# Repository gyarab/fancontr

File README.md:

# Rozcestník

- `dokumentace.pdf` -- Dokumentace v PDF
- `dokumentace/` -- Zdrojové soubory dokumentace
- `hw_foto/` -- Fotodokumentace hardwaru
- `firmware/` -- Zdrojový kód firmwaru
- `kicad_v1/` -- KiCad projekt hardwaru v1
	- `kicad_v1/fancontr.pdf` -- PDF schématu
	- `kicad_v1/bom/ibom.html` -- Interaktivní zobrazení tištěného spoje
- `kicad_v2_wip/` -- KiCad projekt hardwaru v2 (nefinální!)
	- `kicad_v2_wip/fancontr.pdf` -- PDF schématu
	- `kicad_v2_wip/bom/ibom.html` -- Interaktivní zobrazení tištěného spoje

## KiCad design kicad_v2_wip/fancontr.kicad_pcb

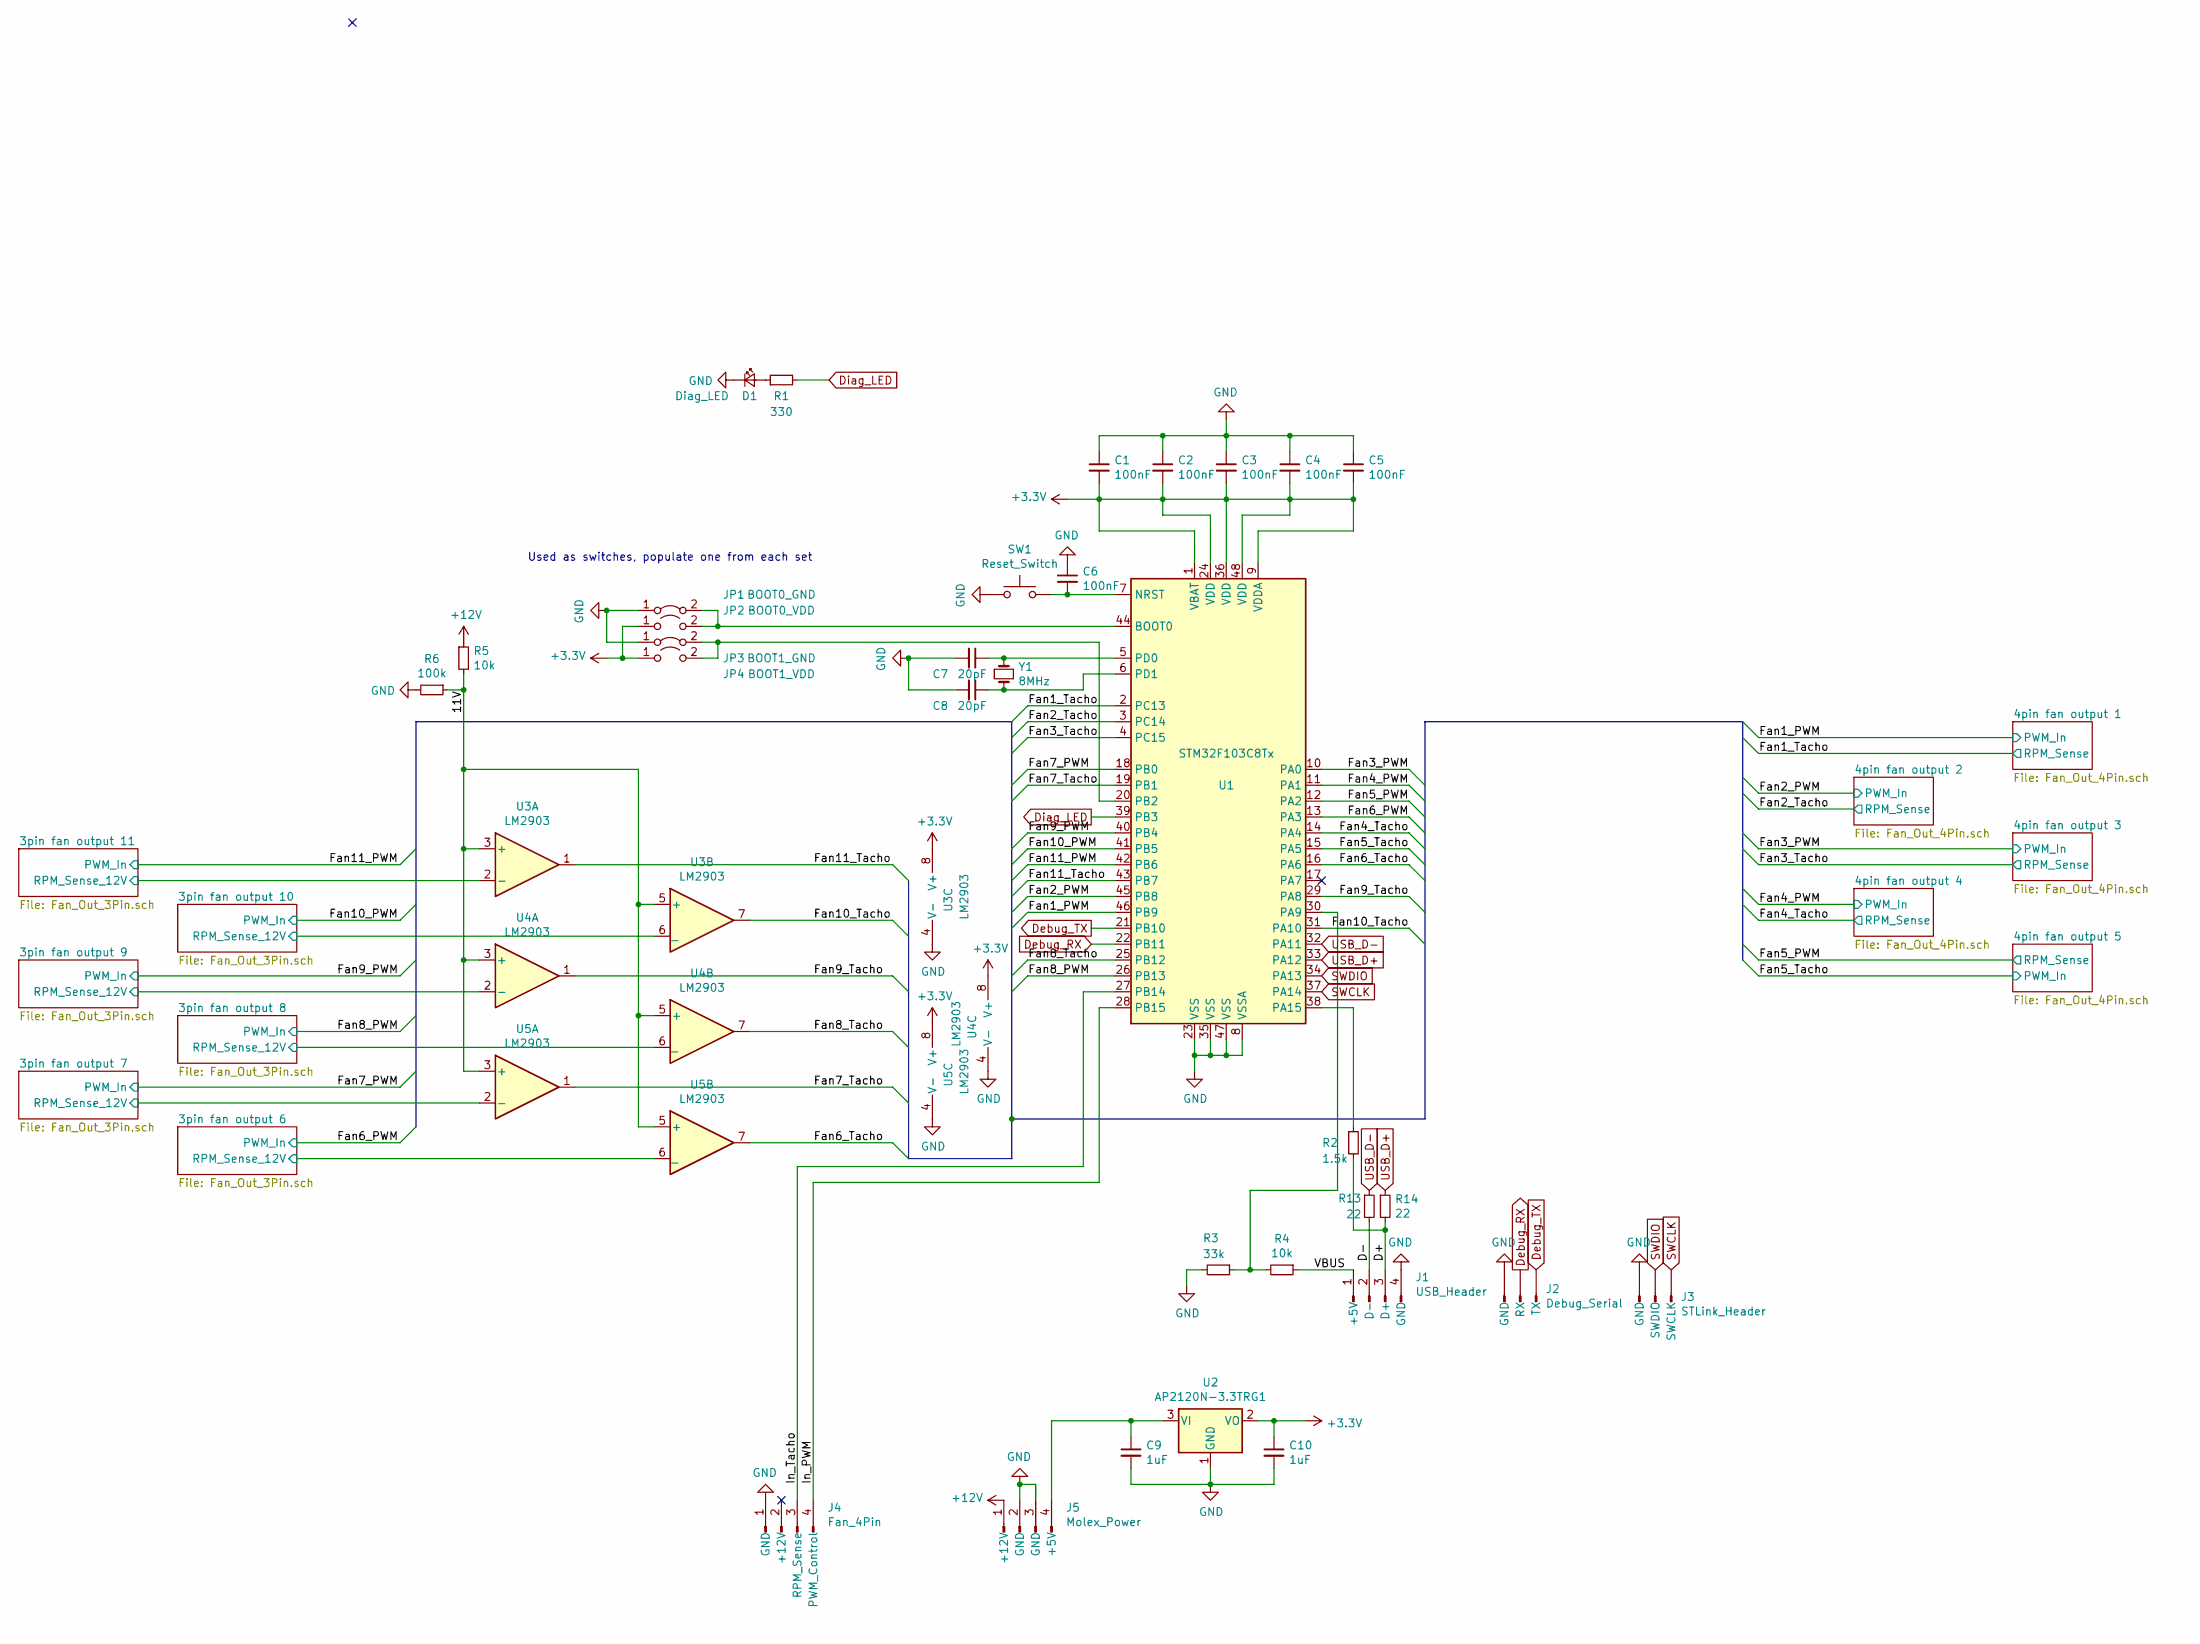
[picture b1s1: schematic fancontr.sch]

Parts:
C1, C2, C3, C4, C5, C6: 100nF; C_0805_2012Metric_Pad1.15x1.40mm_HandSolder
C7, C8: 20pF; C_0805_2012Metric_Pad1.15x1.40mm_HandSolder
C9, C10: 1uF; C_0805_2012Metric_Pad1.15x1.40mm_HandSolder
D1: Diag_LED; LED_0805_2012Metric_Castellated
J1: USB_Header; PinHeader_1x04_P2.54mm_Horizontal_NoSilk
J2: Debug_Serial; PinHeader_1x03_P2.54mm_Vertical
J3: STLink_Header; PinHeader_1x03_P2.54mm_Vertical
J4: Fan_4Pin; PinHeader_1x04_P2.54mm_Horizontal_NoSilk
J5: Molex_Power; MATE-N-LOK 641737-1
JP1: BOOT0_GND; SolderJumper-2_P1.3mm_Open_Pad1.0x1.5mm
JP2: BOOT0_VDD; SolderJumper-2_P1.3mm_Open_Pad1.0x1.5mm
JP3: BOOT1_GND; SolderJumper-2_P1.3mm_Open_Pad1.0x1.5mm
JP4: BOOT1_VDD; SolderJumper-2_P1.3mm_Open_Pad1.0x1.5mm
R1: 330; R_0805_2012Metric_Pad1.15x1.40mm_HandSolder
R2: 1.5k; R_0805_2012Metric_Pad1.15x1.40mm_HandSolder
R3: 33k; R_0805_2012Metric_Pad1.15x1.40mm_HandSolder
R4, R5: 10k; R_0805_2012Metric_Pad1.15x1.40mm_HandSolder
R6: 100k; R_0805_2012Metric_Pad1.15x1.40mm_HandSolder
R13, R14: 22; R_0805_2012Metric_Pad1.15x1.40mm_HandSolder
SW1: Reset_Switch; SolderJumper-2_P1.3mm_Open_Pad1.0x1.5mm
U1: STM32F103C8Tx; LQFP-48_7x7mm_P0.5mm
U2: AP2120N-3.3TRG1; SOT-23_Handsoldering
U3, U4, U5: LM2903; SOIC-8_3.9x4.9mm_P1.27mm
Y1: 8MHz; Crystal_SMD_HC49-SD

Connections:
+3V3: C1.2, C2.2, C3.2, C4.2, C5.2, C10.1, JP2.1 (A), JP4.1 (A), U1.1 (VBAT), U1.9 (VDDA), U1.24 (VDD), U1.36 (VDD), U1.48 (VDD), U2.2 (VO), U3.8 (V+), U4.8 (V+), U5.8 (V+)
+12V: J5.1 (+12V), R5.1; also elsewhere on the board
/3pin fan output 6/RPM_Sense_12V: U5.6 (_); also elsewhere on the board
/3pin fan output 7/RPM_Sense_12V: U5.2 (-); also elsewhere on the board
/3pin fan output 8/RPM_Sense_12V: U4.6 (_); also elsewhere on the board
/3pin fan output 9/RPM_Sense_12V: U4.2 (-); also elsewhere on the board
/3pin fan output 10/RPM_Sense_12V: U3.6 (_); also elsewhere on the board
/3pin fan output 11/RPM_Sense_12V: U3.2 (-); also elsewhere on the board
/11V: R5.2, R6.1, U3.3 (+), U3.5 (+), U4.3 (+), U4.5 (+), U5.3 (+), U5.5 (+)
/D+: J1.3 (D+), R2.2, R14.2
/D-: J1.2 (D-), R13.2
/Fan1_PWM: U1.46 (PB9); also elsewhere on the board
/Fan1_Tacho: U1.2 (PC13); also elsewhere on the board
/Fan2_PWM: U1.45 (PB8); also elsewhere on the board
/Fan2_Tacho: U1.3 (PC14); also elsewhere on the board
/Fan3_PWM: U1.10 (PA0); also elsewhere on the board
/Fan3_Tacho: U1.4 (PC15); also elsewhere on the board
/Fan4_PWM: U1.11 (PA1); also elsewhere on the board
/Fan4_Tacho: U1.14 (PA4); also elsewhere on the board
/Fan5_PWM: U1.12 (PA2); also elsewhere on the board
/Fan5_Tacho: U1.15 (PA5); also elsewhere on the board
/Fan6_PWM: U1.13 (PA3); also elsewhere on the board
/Fan6_Tacho: U1.16 (PA6), U5.7
/Fan7_PWM: U1.18 (PB0); also elsewhere on the board
/Fan7_Tacho: U1.19 (PB1), U5.1
/Fan8_PWM: U1.26 (PB13); also elsewhere on the board
/Fan8_Tacho: U1.25 (PB12), U4.7
/Fan9_PWM: U1.40 (PB4); also elsewhere on the board
/Fan9_Tacho: U1.29 (PA8), U4.1
/Fan10_PWM: U1.41 (PB5); also elsewhere on the board
/Fan10_Tacho: U1.31 (PA10), U3.7
/Fan11_PWM: U1.42 (PB6); also elsewhere on the board
/Fan11_Tacho: U1.43 (PB7), U3.1
/In_PWM: J4.4 (PWM_Control), U1.28 (PB15)
/In_Tacho: J4.3 (RPM_Sense), U1.27 (PB14)
/VBUS: J1.1 (+5V), R4.1
Debug_RX: J2.2 (RX), U1.22 (PB11)
Debug_TX: J2.3 (TX), U1.21 (PB10)
Diag_LED: R1.2, U1.39 (PB3)
GND: C1.1, C2.1, C3.1, C4.1, C5.1, C6.1, C7.2, C8.2, C9.2, C10.2, D1.1 (K), J1.4 (GND), J2.1 (GND), J3.1 (GND), J4.1 (GND), J5.2 (GND), J5.3 (GND), JP1.1 (A), JP3.1 (A), R3.2, R6.2, SW1.1, U1.8 (VSSA), U1.23 (VSS), U1.35 (VSS), U1.47 (VSS), U2.1 (GND), U3.4 (V-), U4.4 (V-), U5.4 (V-); also elsewhere on the board
unnamed: C6.2, SW1.2, U1.7 (NRST)
unnamed: C7.1, U1.5 (PD0), Y1.1
unnamed: C8.1, U1.6 (PD1), Y1.2
unnamed: C9.1, J5.4 (+5V), U2.3 (VI)
unnamed: D1.2 (A), R1.1
unnamed: JP1.2 (B), JP2.2 (B), U1.44 (BOOT0)
unnamed: JP3.2 (B), JP4.2 (B), U1.20 (PB2)
unnamed: R2.1, U1.38 (PA15)
unnamed: R3.1, R4.2, U1.30 (PA9)
SWCLK: J3.3 (SWCLK), U1.37 (PA14)
SWDIO: J3.2 (SWDIO), U1.34 (PA13)
USB_D+: R14.1, U1.33 (PA12)
USB_D-: R13.1, U1.32 (PA11)

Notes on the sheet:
Used as switches, populate one from each set

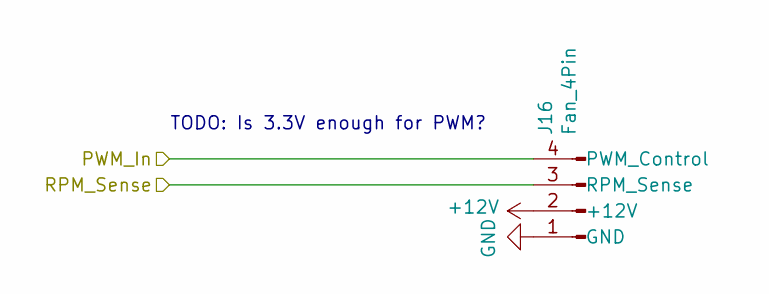
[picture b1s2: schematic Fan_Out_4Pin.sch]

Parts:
J6: Fan_4Pin; PinHeader_1x04_P2.54mm_Horizontal_NoSilk

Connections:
+12V: J6.2 (+12V); also elsewhere on the board
/Fan1_PWM: J6.4 (PWM_Control); also elsewhere on the board
/Fan1_Tacho: J6.3 (RPM_Sense); also elsewhere on the board
GND: J6.1 (GND); also elsewhere on the board

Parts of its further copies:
J7, J8, J9, J16: Fan_4Pin; PinHeader_1x04_P2.54mm_Horizontal_NoSilk

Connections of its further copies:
+12V: J7.2 (+12V), J8.2 (+12V), J9.2 (+12V), J16.2 (+12V); also elsewhere on the board
/Fan2_PWM: J7.4 (PWM_Control); also elsewhere on the board
/Fan2_Tacho: J7.3 (RPM_Sense); also elsewhere on the board
/Fan3_PWM: J8.4 (PWM_Control); also elsewhere on the board
/Fan3_Tacho: J8.3 (RPM_Sense); also elsewhere on the board
/Fan4_PWM: J9.4 (PWM_Control); also elsewhere on the board
/Fan4_Tacho: J9.3 (RPM_Sense); also elsewhere on the board
/Fan5_PWM: J16.3 (RPM_Sense); also elsewhere on the board
/Fan5_Tacho: J16.4 (PWM_Control); also elsewhere on the board
GND: J7.1 (GND), J8.1 (GND), J9.1 (GND), J16.1 (GND); also elsewhere on the board

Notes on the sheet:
TODO: Is 3.3V enough for PWM?

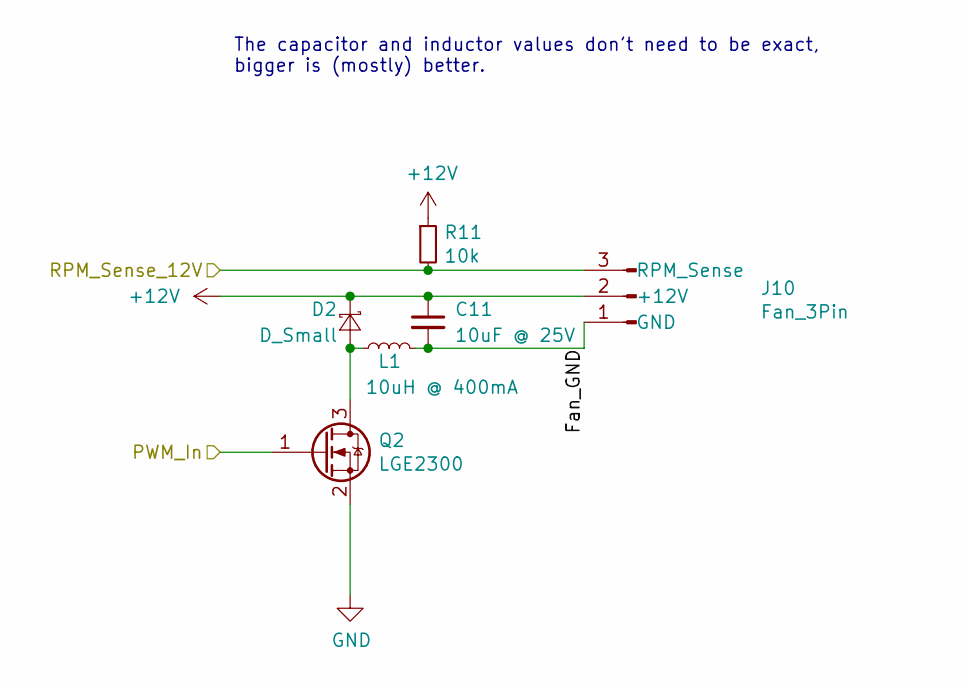
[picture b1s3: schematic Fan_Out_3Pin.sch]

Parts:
C16: 10uF @ 25V; C_0805_2012Metric_Pad1.15x1.40mm_HandSolder
D2: D_Small; D_SOD-323_HandSoldering
J15: Fan_3Pin; PinHeader_1x03_P2.54mm_Horizontal_NoSilk
L5: 10uH @ 400mA; L_0805_2012Metric_Pad1.15x1.40mm_HandSolder
Q7: LGE2300; TSOT-23
R12: 10k; R_0805_2012Metric_Pad1.15x1.40mm_HandSolder

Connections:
+12V: C16.1, D2.1 (K), J15.2 (+12V), R12.1; also elsewhere on the board
/3pin fan output 11/RPM_Sense_12V: J15.3 (RPM_Sense), R12.2; also elsewhere on the board
/Fan11_PWM: Q7.1 (G); also elsewhere on the board
GND: Q7.2 (S); also elsewhere on the board

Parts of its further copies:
C11, C12, C13, C14, C15: 10uF @ 25V; C_0805_2012Metric_Pad1.15x1.40mm_HandSolder
D3, D4, D5, D6, D7: D_Small; D_SOD-323_HandSoldering
J10, J11, J12, J13, J14: Fan_3Pin; PinHeader_1x03_P2.54mm_Horizontal_NoSilk
L1, L2, L3, L4, L6: 10uH @ 400mA; L_0805_2012Metric_Pad1.15x1.40mm_HandSolder
Q2, Q3, Q4, Q5, Q6: LGE2300; TSOT-23
R7, R8, R9, R10, R11: 10k; R_0805_2012Metric_Pad1.15x1.40mm_HandSolder

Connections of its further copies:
+12V: C11.1, C12.1, C13.1, C14.1, C15.1, D3.1 (K), D4.1 (K), D5.1 (K), D6.1 (K), D7.1 (K), J10.2 (+12V), J11.2 (+12V), J12.2 (+12V), J13.2 (+12V), J14.2 (+12V), R7.1, R8.1, R9.1, R10.1, R11.1; also elsewhere on the board
/3pin fan output 6/Fan_GND: C11.2, J10.1 (GND), L1.2
/3pin fan output 6/RPM_Sense_12V: J10.3 (RPM_Sense), R11.2; also elsewhere on the board
/3pin fan output 7/Fan_GND: C12.2, J11.1 (GND), L2.2
/3pin fan output 7/RPM_Sense_12V: J11.3 (RPM_Sense), R7.2; also elsewhere on the board
/3pin fan output 8/Fan_GND: C13.2, J12.1 (GND), L3.2
/3pin fan output 8/RPM_Sense_12V: J12.3 (RPM_Sense), R8.2; also elsewhere on the board
/3pin fan output 9/Fan_GND: C14.2, J13.1 (GND), L4.2
/3pin fan output 9/RPM_Sense_12V: J13.3 (RPM_Sense), R9.2; also elsewhere on the board
/3pin fan output 10/RPM_Sense_12V: J14.3 (RPM_Sense), R10.2; also elsewhere on the board
/Fan6_PWM: Q2.1 (G); also elsewhere on the board
/Fan7_PWM: Q3.1 (G); also elsewhere on the board
/Fan8_PWM: Q4.1 (G); also elsewhere on the board
/Fan9_PWM: Q5.1 (G); also elsewhere on the board
/Fan10_PWM: Q6.1 (G); also elsewhere on the board
GND: Q2.2 (S), Q3.2 (S), Q4.2 (S), Q5.2 (S), Q6.2 (S); also elsewhere on the board
unnamed: D3.2 (A), L2.1, Q3.3 (D)
unnamed: D4.2 (A), L3.1, Q4.3 (D)
unnamed: D5.2 (A), L4.1, Q5.3 (D)

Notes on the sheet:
The capacitor and inductor values don't need to be exact, bigger is (mostly) better.

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
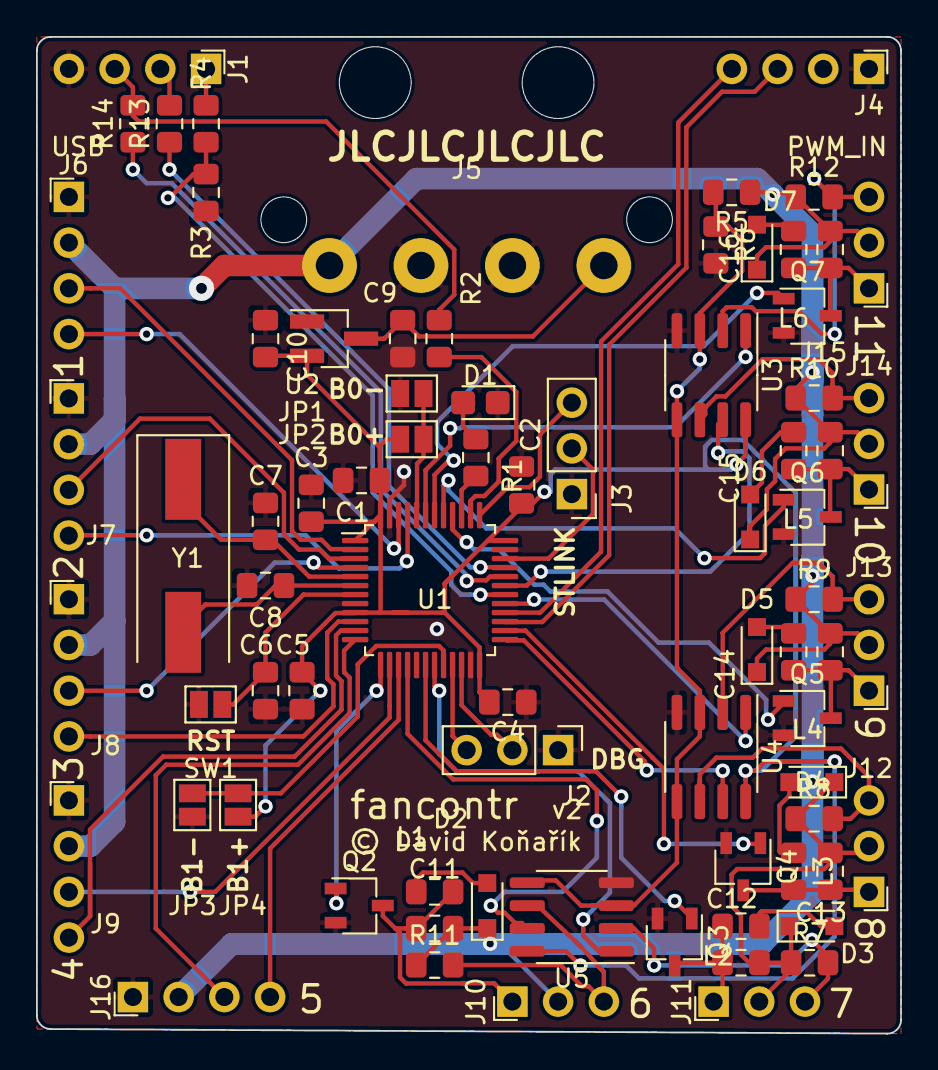
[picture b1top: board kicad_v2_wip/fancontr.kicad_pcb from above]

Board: 2 copper layers, 48.0 x 55.4 mm, 76 parts (0 on the bottom side), 65 nets.

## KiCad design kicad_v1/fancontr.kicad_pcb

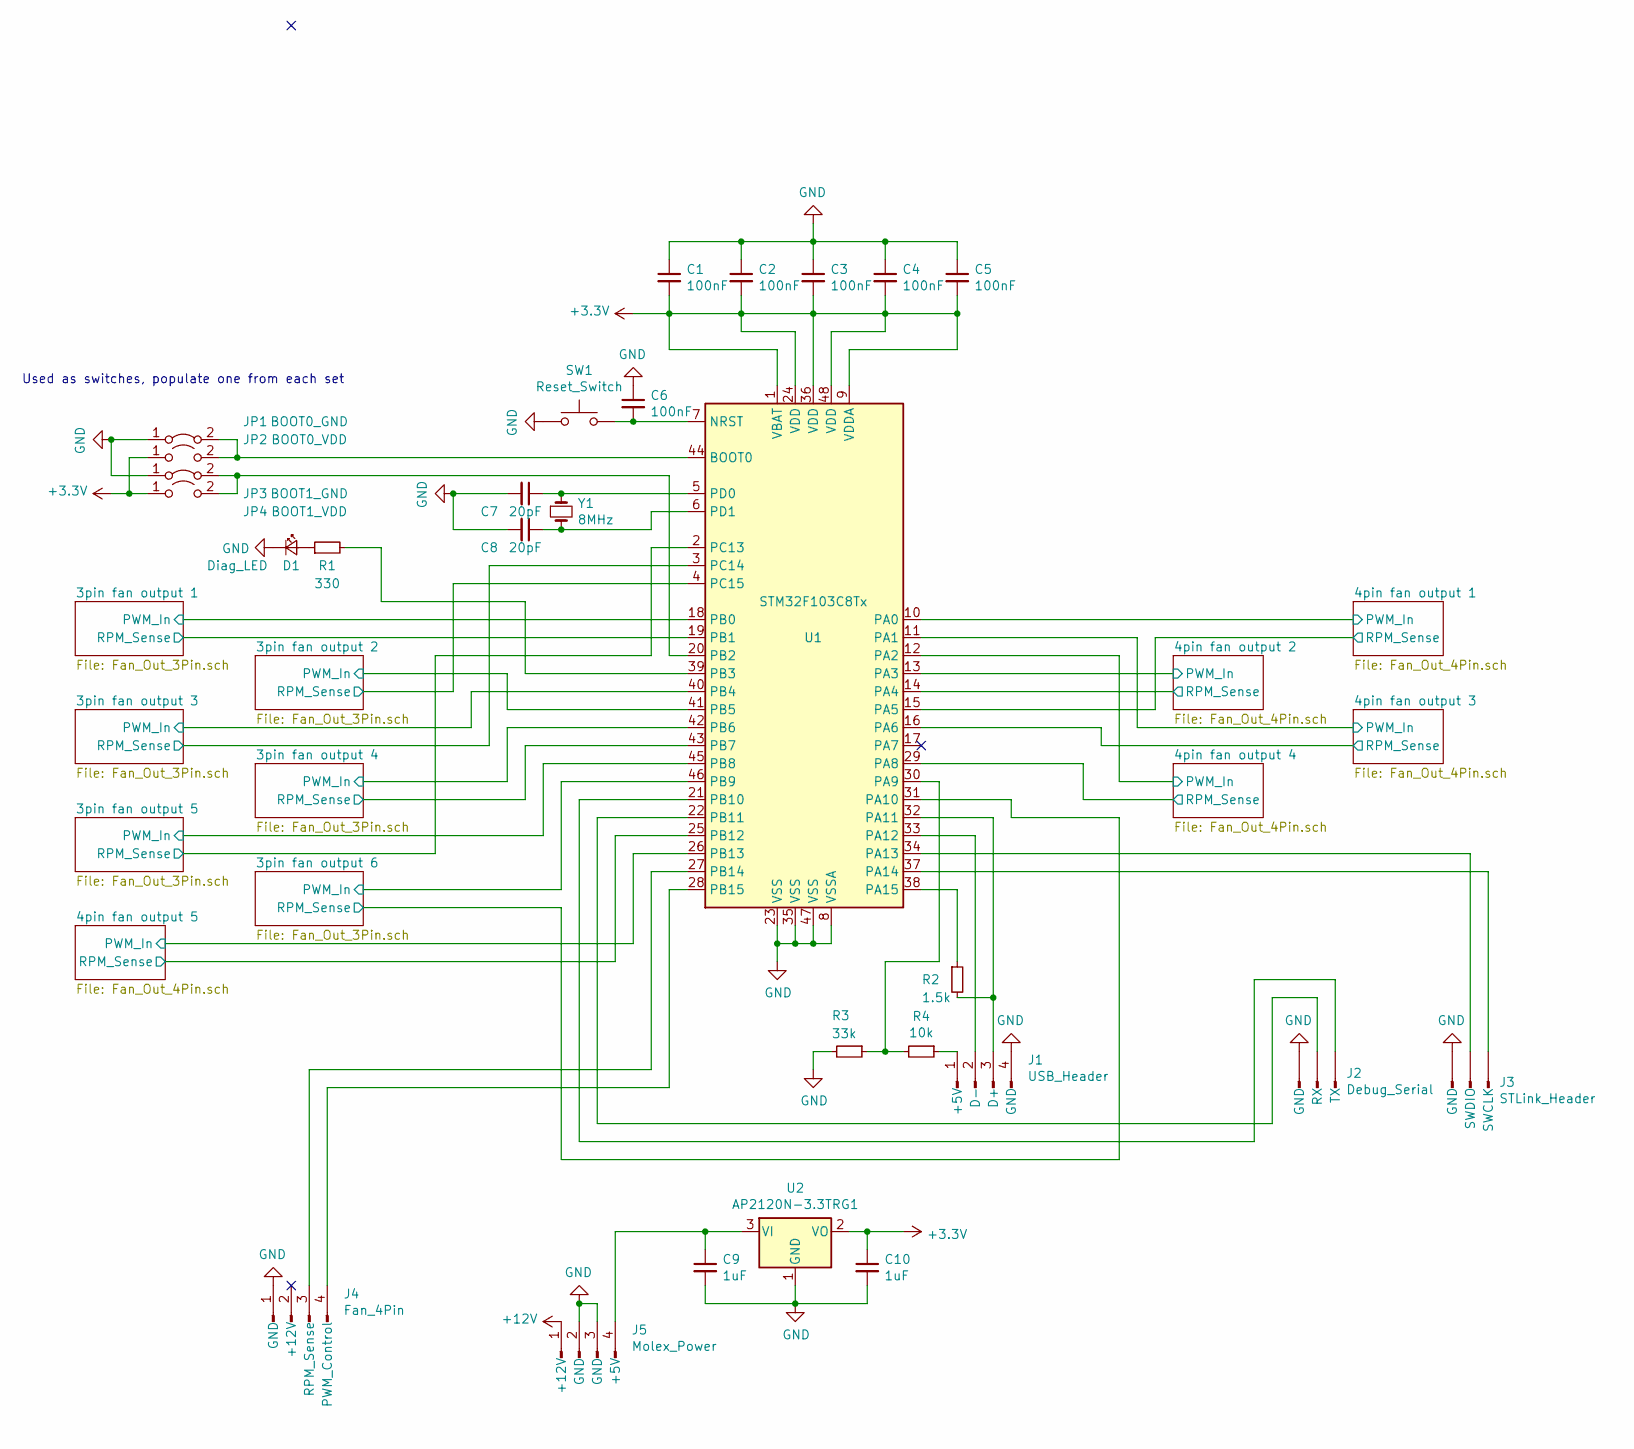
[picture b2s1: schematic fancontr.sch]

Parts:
C1, C2, C3, C4, C5, C6: 100nF; C_0805_2012Metric_Pad1.15x1.40mm_HandSolder
C7, C8: 20pF; C_0805_2012Metric_Pad1.15x1.40mm_HandSolder
C9, C10: 1uF; C_0805_2012Metric_Pad1.15x1.40mm_HandSolder
D1: Diag_LED; LED_0805_2012Metric_Castellated
J1: USB_Header; PinHeader_1x04_P2.54mm_Horizontal_NoSilk
J2: Debug_Serial; PinHeader_1x03_P2.54mm_Vertical
J3: STLink_Header; PinHeader_1x03_P2.54mm_Vertical
J4: Fan_4Pin; PinHeader_1x04_P2.54mm_Horizontal_NoSilk
J5: Molex_Power; MATE-N-LOK 641737-1
JP1: BOOT0_GND; SolderJumper-2_P1.3mm_Open_Pad1.0x1.5mm
JP2: BOOT0_VDD; SolderJumper-2_P1.3mm_Open_Pad1.0x1.5mm
JP3: BOOT1_GND; SolderJumper-2_P1.3mm_Open_Pad1.0x1.5mm
JP4: BOOT1_VDD; SolderJumper-2_P1.3mm_Open_Pad1.0x1.5mm
R1: 330; R_0805_2012Metric_Pad1.15x1.40mm_HandSolder
R2: 1.5k; R_0805_2012Metric_Pad1.15x1.40mm_HandSolder
R3: 33k; R_0805_2012Metric_Pad1.15x1.40mm_HandSolder
R4: 10k; R_0805_2012Metric_Pad1.15x1.40mm_HandSolder
SW1: Reset_Switch; SolderJumper-2_P1.3mm_Open_Pad1.0x1.5mm
U1: STM32F103C8Tx; LQFP-48_7x7mm_P0.5mm
U2: AP2120N-3.3TRG1; SOT-23_Handsoldering
Y1: 8MHz; Crystal_SMD_HC49-SD

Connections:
+3V3: C1.2, C2.2, C3.2, C4.2, C5.2, C10.1, JP2.1 (A), JP4.1 (A), U1.1 (VBAT), U1.9 (VDDA), U1.24 (VDD), U1.36 (VDD), U1.48 (VDD), U2.2 (VO)
+12V: J5.1 (+12V); also elsewhere on the board
/3pin fan output 1/PWM_In: U1.18 (PB0); also elsewhere on the board
/3pin fan output 1/RPM_Sense: U1.19 (PB1); also elsewhere on the board
/3pin fan output 2/PWM_In: U1.41 (PB5); also elsewhere on the board
/3pin fan output 2/RPM_Sense: U1.4 (PC15); also elsewhere on the board
/3pin fan output 3/PWM_In: U1.40 (PB4); also elsewhere on the board
/3pin fan output 3/RPM_Sense: U1.3 (PC14); also elsewhere on the board
/3pin fan output 4/PWM_In: U1.42 (PB6); also elsewhere on the board
/3pin fan output 4/RPM_Sense: U1.43 (PB7); also elsewhere on the board
/3pin fan output 5/PWM_In: U1.45 (PB8); also elsewhere on the board
/3pin fan output 5/RPM_Sense: U1.2 (PC13); also elsewhere on the board
/3pin fan output 6/PWM_In: U1.46 (PB9); also elsewhere on the board
/3pin fan output 6/RPM_Sense: U1.31 (PA10); also elsewhere on the board
/4pin fan output 1/PWM_In: U1.10 (PA0); also elsewhere on the board
/4pin fan output 1/RPM_Sense: U1.15 (PA5); also elsewhere on the board
/4pin fan output 2/PWM_In: U1.13 (PA3); also elsewhere on the board
/4pin fan output 2/RPM_Sense: U1.14 (PA4); also elsewhere on the board
/4pin fan output 3/PWM_In: U1.11 (PA1); also elsewhere on the board
/4pin fan output 3/RPM_Sense: U1.16 (PA6); also elsewhere on the board
/4pin fan output 4/PWM_In: U1.12 (PA2); also elsewhere on the board
/4pin fan output 4/RPM_Sense: U1.29 (PA8); also elsewhere on the board
/4pin fan output 5/PWM_In: U1.26 (PB13); also elsewhere on the board
/4pin fan output 5/RPM_Sense: U1.25 (PB12); also elsewhere on the board
GND: C1.1, C2.1, C3.1, C4.1, C5.1, C6.1, C7.2, C8.2, C9.2, C10.2, D1.1 (K), J1.4 (GND), J2.1 (GND), J3.1 (GND), J4.1 (GND), J5.2 (GND), J5.3 (GND), JP1.1 (A), JP3.1 (A), R3.2, SW1.1, U1.8 (VSSA), U1.23 (VSS), U1.35 (VSS), U1.47 (VSS), U2.1 (GND); also elsewhere on the board
unnamed: C6.2, SW1.2, U1.7 (NRST)
unnamed: C7.1, U1.5 (PD0), Y1.1
unnamed: C8.1, U1.6 (PD1), Y1.2
unnamed: C9.1, J5.4 (+5V), U2.3 (VI)
unnamed: D1.2 (A), R1.1
unnamed: J1.1 (+5V), R4.1
unnamed: J1.2 (D-), U1.33 (PA12)
unnamed: J1.3 (D+), R2.2, U1.32 (PA11)
unnamed: J2.2 (RX), U1.22 (PB11)
unnamed: J2.3 (TX), U1.21 (PB10)
unnamed: J3.2 (SWDIO), U1.34 (PA13)
unnamed: J3.3 (SWCLK), U1.37 (PA14)
unnamed: J4.3 (RPM_Sense), U1.27 (PB14)
unnamed: J4.4 (PWM_Control), U1.28 (PB15)
unnamed: JP1.2 (B), JP2.2 (B), U1.44 (BOOT0)
unnamed: JP3.2 (B), JP4.2 (B), U1.20 (PB2)
unnamed: R1.2, U1.39 (PB3)
unnamed: R2.1, U1.38 (PA15)
unnamed: R3.1, R4.2, U1.30 (PA9)

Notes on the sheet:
Used as switches, populate one from each set

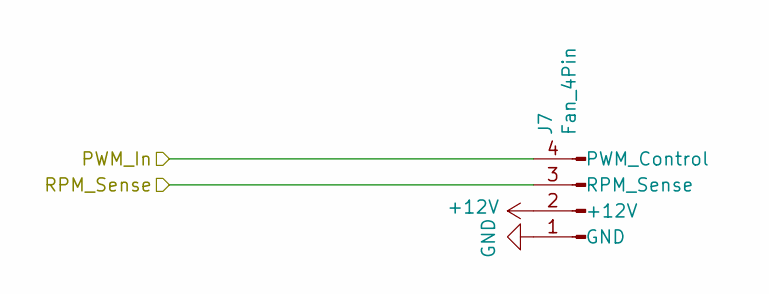
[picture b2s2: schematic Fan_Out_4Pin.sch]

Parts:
J6: Fan_4Pin; PinHeader_1x04_P2.54mm_Horizontal_NoSilk

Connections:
+12V: J6.2 (+12V); also elsewhere on the board
/4pin fan output 1/PWM_In: J6.4 (PWM_Control); also elsewhere on the board
/4pin fan output 1/RPM_Sense: J6.3 (RPM_Sense); also elsewhere on the board
GND: J6.1 (GND); also elsewhere on the board

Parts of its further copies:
J7, J8, J9, J16: Fan_4Pin; PinHeader_1x04_P2.54mm_Horizontal_NoSilk

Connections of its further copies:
+12V: J7.2 (+12V), J8.2 (+12V), J9.2 (+12V), J16.2 (+12V); also elsewhere on the board
/4pin fan output 2/PWM_In: J7.4 (PWM_Control); also elsewhere on the board
/4pin fan output 2/RPM_Sense: J7.3 (RPM_Sense); also elsewhere on the board
/4pin fan output 3/PWM_In: J8.4 (PWM_Control); also elsewhere on the board
/4pin fan output 3/RPM_Sense: J8.3 (RPM_Sense); also elsewhere on the board
/4pin fan output 4/PWM_In: J9.4 (PWM_Control); also elsewhere on the board
/4pin fan output 4/RPM_Sense: J9.3 (RPM_Sense); also elsewhere on the board
/4pin fan output 5/PWM_In: J16.4 (PWM_Control); also elsewhere on the board
/4pin fan output 5/RPM_Sense: J16.3 (RPM_Sense); also elsewhere on the board
GND: J7.1 (GND), J8.1 (GND), J9.1 (GND), J16.1 (GND); also elsewhere on the board

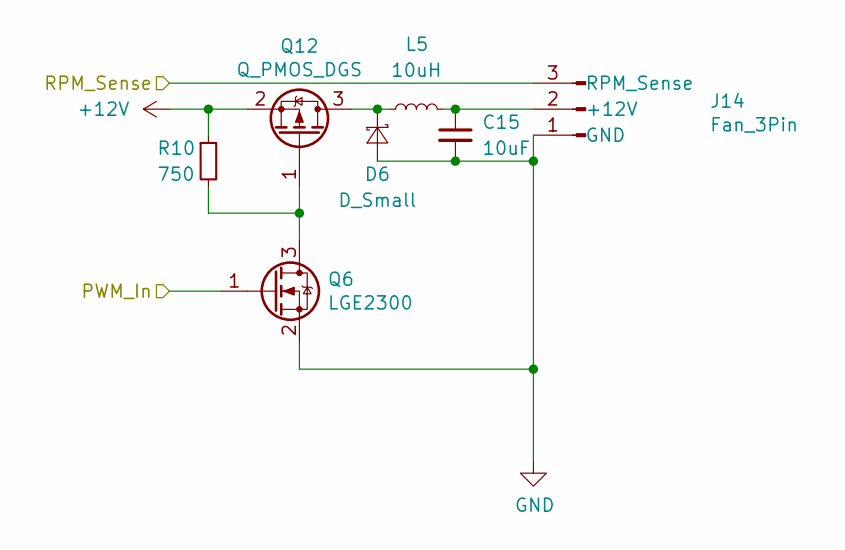
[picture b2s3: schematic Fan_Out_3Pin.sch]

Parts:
C16: 10uF; C_0805_2012Metric_Pad1.15x1.40mm_HandSolder
D2: D_Small; D_SOD-323_HandSoldering
J15: Fan_3Pin; PinHeader_1x03_P2.54mm_Horizontal_NoSilk
L5: 10uH; L_0805_2012Metric_Pad1.15x1.40mm_HandSolder
Q7: LGE2300; TSOT-23
Q13: Q_PMOS_DGS; TSOT-23
R11: 750; R_0805_2012Metric_Pad1.15x1.40mm_HandSolder

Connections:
+12V: Q13.2 (S), R11.1; also elsewhere on the board
/3pin fan output 1/PWM_In: Q7.1 (G); also elsewhere on the board
/3pin fan output 1/RPM_Sense: J15.3 (RPM_Sense); also elsewhere on the board
GND: C16.2, D2.2 (A), J15.1 (GND), Q7.2 (S); also elsewhere on the board
unnamed: Q7.3 (D), Q13.1 (G), R11.2

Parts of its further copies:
C11, C12, C13, C14, C15: 10uF; C_0805_2012Metric_Pad1.15x1.40mm_HandSolder
D3, D4, D5, D6, D7: D_Small; D_SOD-323_HandSoldering
J10, J11, J12, J13, J14: Fan_3Pin; PinHeader_1x03_P2.54mm_Horizontal_NoSilk
L1, L2, L3, L4, L6: 10uH; L_0805_2012Metric_Pad1.15x1.40mm_HandSolder
Q2, Q3, Q4, Q5, Q6: LGE2300; TSOT-23
Q8, Q9, Q10, Q11, Q12: Q_PMOS_DGS; TSOT-23
R6, R7, R8, R9, R10: 750; R_0805_2012Metric_Pad1.15x1.40mm_HandSolder

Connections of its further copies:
+12V: Q8.2 (S), Q9.2 (S), Q10.2 (S), Q11.2 (S), Q12.2 (S), R6.1, R7.1, R8.1, R9.1, R10.1; also elsewhere on the board
/3pin fan output 2/PWM_In: Q6.1 (G); also elsewhere on the board
/3pin fan output 2/RPM_Sense: J14.3 (RPM_Sense); also elsewhere on the board
/3pin fan output 3/PWM_In: Q3.1 (G); also elsewhere on the board
/3pin fan output 3/RPM_Sense: J11.3 (RPM_Sense); also elsewhere on the board
/3pin fan output 4/PWM_In: Q4.1 (G); also elsewhere on the board
/3pin fan output 4/RPM_Sense: J12.3 (RPM_Sense); also elsewhere on the board
/3pin fan output 5/PWM_In: Q5.1 (G); also elsewhere on the board
/3pin fan output 5/RPM_Sense: J13.3 (RPM_Sense); also elsewhere on the board
/3pin fan output 6/PWM_In: Q2.1 (G); also elsewhere on the board
/3pin fan output 6/RPM_Sense: J10.3 (RPM_Sense); also elsewhere on the board
GND: C11.2, C12.2, C13.2, C14.2, C15.2, D3.2 (A), D4.2 (A), D5.2 (A), D6.2 (A), D7.2 (A), J10.1 (GND), J11.1 (GND), J12.1 (GND), J13.1 (GND), J14.1 (GND), Q2.2 (S), Q3.2 (S), Q4.2 (S), Q5.2 (S), Q6.2 (S); also elsewhere on the board
unnamed: C11.1, J10.2 (+12V), L1.2
unnamed: C12.1, J11.2 (+12V), L2.2
unnamed: C13.1, J12.2 (+12V), L3.2
unnamed: C14.1, J13.2 (+12V), L4.2
unnamed: D3.1 (K), L2.1, Q9.3 (D)
unnamed: D4.1 (K), L3.1, Q10.3 (D)
unnamed: D5.1 (K), L4.1, Q11.3 (D)
unnamed: Q2.3 (D), Q8.1 (G), R6.2
unnamed: Q3.3 (D), Q9.1 (G), R7.2
unnamed: Q4.3 (D), Q10.1 (G), R8.2
unnamed: Q5.3 (D), Q11.1 (G), R9.2
unnamed: Q6.3 (D), Q12.1 (G), R10.2

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
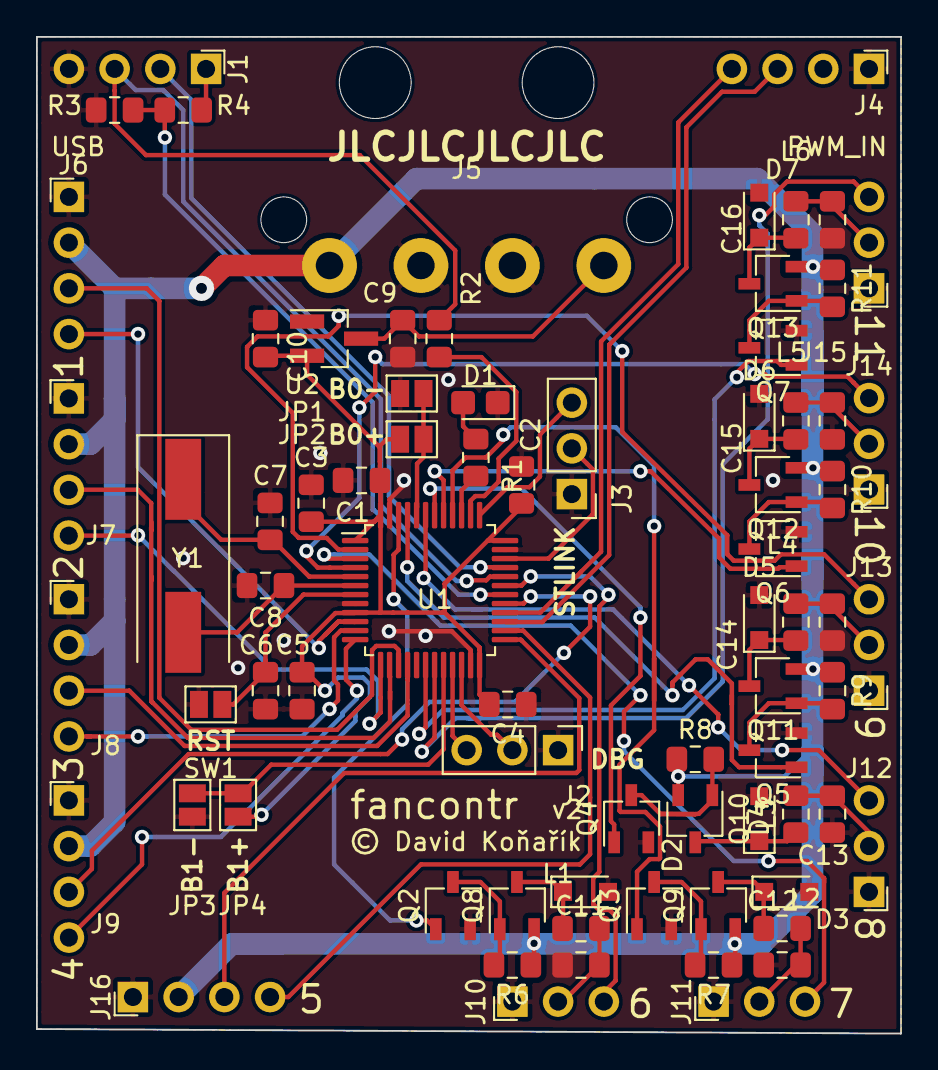
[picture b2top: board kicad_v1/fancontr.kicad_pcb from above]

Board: 2 copper layers, 48.0 x 55.4 mm, 75 parts (0 on the bottom side), 62 nets.

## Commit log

2020-04-29 Hardware v1
2020-04-29 Hardware v2 WIP
2020-04-29 Firmware source code
2020-04-30 Dokumentace
2020-04-30 Dokumentace v PDF
2020-04-30 Fotografie hardwaru
2020-04-30 Dokumentace - obrázky
2020-04-30 Rozcestník
2020-05-10 Prezentace a poster

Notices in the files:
kicad_v1/fancontr.kicad_pcb:
© David Koňařík
